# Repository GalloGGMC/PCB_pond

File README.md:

# Ponderada de PCB - Semana 6

O repositório apresenta duas pasta, uma com as imagens necessárias e a outra com os arquivos do KiCad

```
└── main
   ├─── fotos
   |    ├── pcb_3d.png
   |    ├── pcb.png
   |    └── esquematico.png
   └─── kicad
        ├── aula-backups
        ├── #auto_saved_files#
        ├── ~aula.kicad_pcb.lck
        ├── ~aula.kicad_sch.lck
        ├── aula.kicad_pcb
        ├── aula.kicad_prl
        ├── aula.kicad_pro
        ├── aula.kicad_sch
        ├── aula.kicad_sch-bak
        ├── aula-B_Cu.svg
        ├── aula-F_Cu.svg
        └── fp-info-cache

```

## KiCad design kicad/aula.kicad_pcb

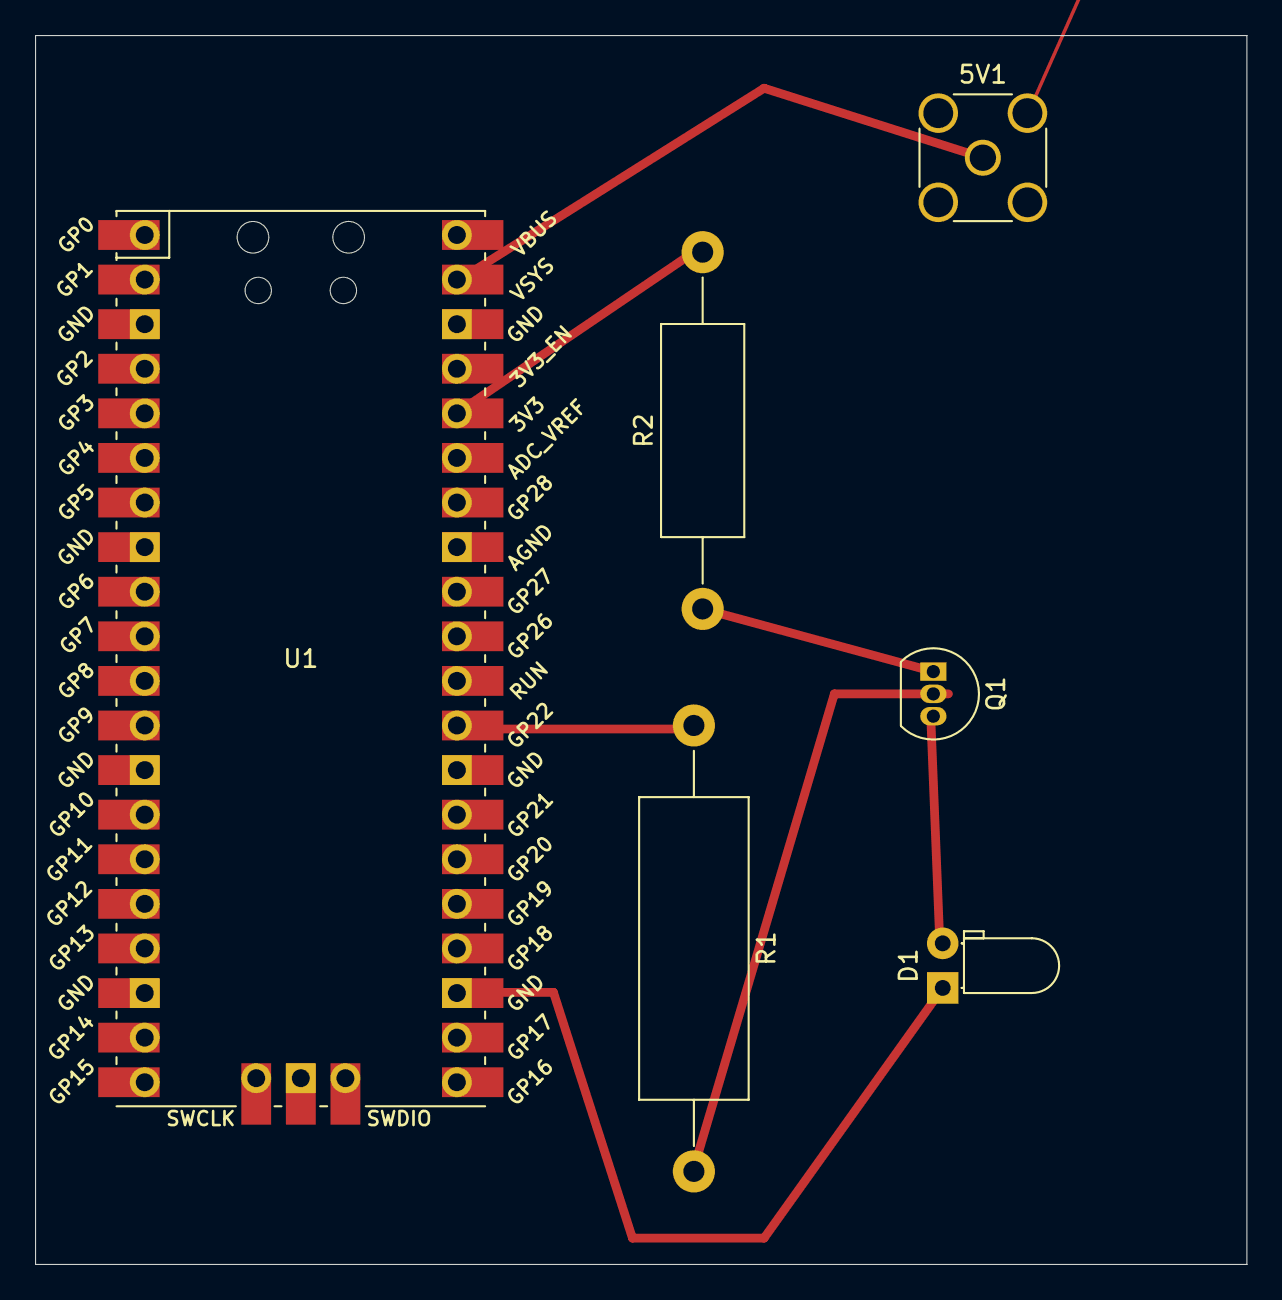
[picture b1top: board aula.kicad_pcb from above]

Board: 2 copper layers, 69.0 x 70.0 mm, 6 parts (0 on the bottom side), 5 nets, no tracks yet.

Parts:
5V1: Battery; SMA_Amphenol_132291-12_Vertical
D1: LED; LED_D3.0mm_Horizontal_O1.27mm_Z2.0mm
Q1: BC548; TO-92_Inline
R1: 10K; R_Axial_DIN0617_L17.0mm_D6.0mm_P25.40mm_Horizontal
R2: 100; R_Axial_DIN0414_L11.9mm_D4.5mm_P20.32mm_Horizontal
U1: Pico; RPi_Pico_SMD_TH

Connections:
GND: 5V1.2 (-), D1.1 (K)
unnamed: 5V1.1 (+), U1.39 (VSYS)
unnamed: D1.2 (A), Q1.3 (E), R2.1
unnamed: Q1.2 (B), R1.2
unnamed: R1.1, R2.2, U1.29 (GPIO22)

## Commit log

2024-03-27 Commit inicial
2024-03-27 correcao README
2024-04-01 Mudança de booster para operação padrão
2024-04-01 adição dos arquivos kicad
